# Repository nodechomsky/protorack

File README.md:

# protorack
A modular system for prototyping tools

The goal of this project is to produce a convergent set of standardized designs for intermodular featuring, fixturing, and dimensioning standard tools used in the process of developing hardware prototypes, specifically in the realm of electronic engineering and it's unique needs.

Standards/Objectives/Goals:

 -Intermodularity within the system to allow creative repurposing and open thought-space for the engineer

 -Interoperability with existing tools with an emphasis on common dimensioning standards found in other tools

 -Open Source and collaborative development of shared standards to allow ideas to be more easily synthesized and shared between collaborators

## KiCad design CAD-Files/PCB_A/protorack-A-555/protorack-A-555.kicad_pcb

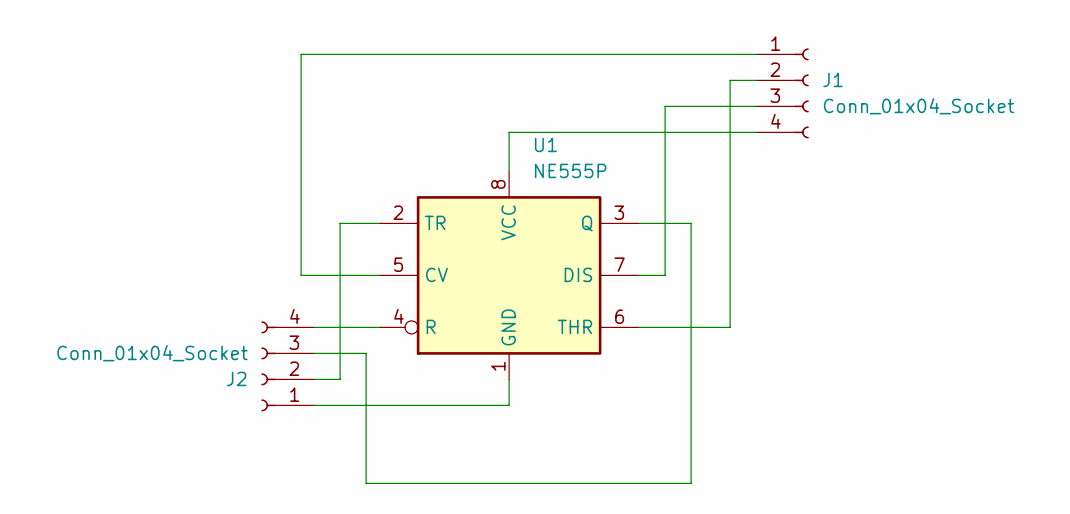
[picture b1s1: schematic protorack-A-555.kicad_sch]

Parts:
J1, J2: Conn_01x04_Socket; PinHeader_1x04_P2.54mm_Vertical
U1: NE555P; DIP-8_W7.62mm

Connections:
unnamed: J1.1, U1.5 (CV)
unnamed: J1.2, U1.6 (THR)
unnamed: J1.3, U1.7 (DIS)
unnamed: J1.4, U1.8 (VCC)
unnamed: J2.1, U1.1 (GND)
unnamed: J2.2, U1.2 (TR)
unnamed: J2.3, U1.3 (Q)
unnamed: J2.4, U1.4 (R)

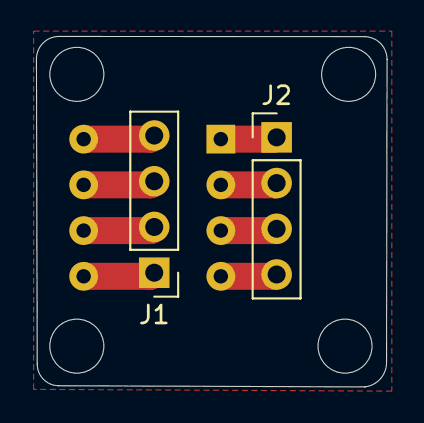
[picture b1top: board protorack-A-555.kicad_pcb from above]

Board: 2 copper layers, 19.5 x 19.5 mm, 3 parts (1 on the bottom side), 8 nets.

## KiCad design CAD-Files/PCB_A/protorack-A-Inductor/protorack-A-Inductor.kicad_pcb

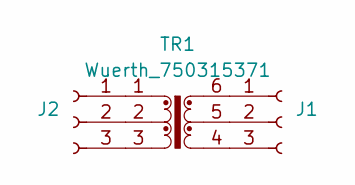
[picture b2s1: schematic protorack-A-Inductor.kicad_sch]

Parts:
J1, J2: Conn_01x03_Socket; PinHeader_1x03_P2.54mm_Vertical
TR1: Wuerth_750315371; Transformer_Wuerth_750315371

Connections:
unnamed: J1.1, TR1.6
unnamed: J1.2, TR1.5
unnamed: J1.3, TR1.4
unnamed: J2.1, TR1.1
unnamed: J2.2, TR1.2
unnamed: J2.3, TR1.3

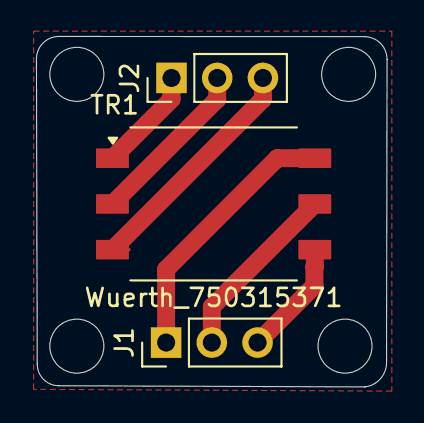
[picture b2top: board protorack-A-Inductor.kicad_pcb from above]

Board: 2 copper layers, 19.5 x 19.5 mm, 3 parts (0 on the bottom side), 6 nets.

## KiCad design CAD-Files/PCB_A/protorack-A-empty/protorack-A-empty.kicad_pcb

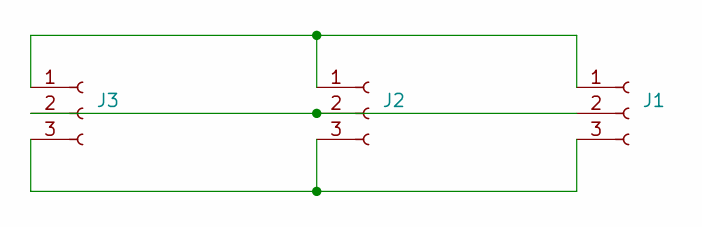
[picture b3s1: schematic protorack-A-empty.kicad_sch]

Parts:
J1, J2, J3: Conn_01x03_Socket; PinHeader_1x03_P2.54mm_Vertical

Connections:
unnamed: J1.1, J2.1, J3.1
unnamed: J1.2, J2.2, J3.2
unnamed: J1.3, J2.3, J3.3

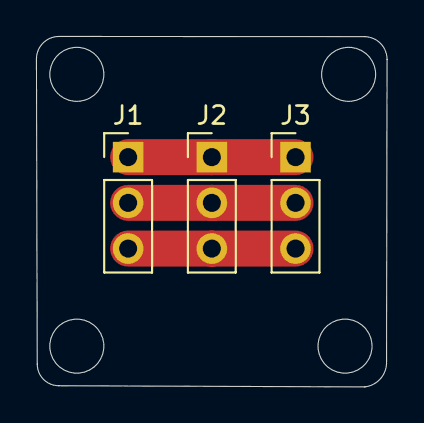
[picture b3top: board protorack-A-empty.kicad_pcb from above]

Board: 2 copper layers, 19.5 x 19.5 mm, 3 parts (0 on the bottom side), 3 nets.

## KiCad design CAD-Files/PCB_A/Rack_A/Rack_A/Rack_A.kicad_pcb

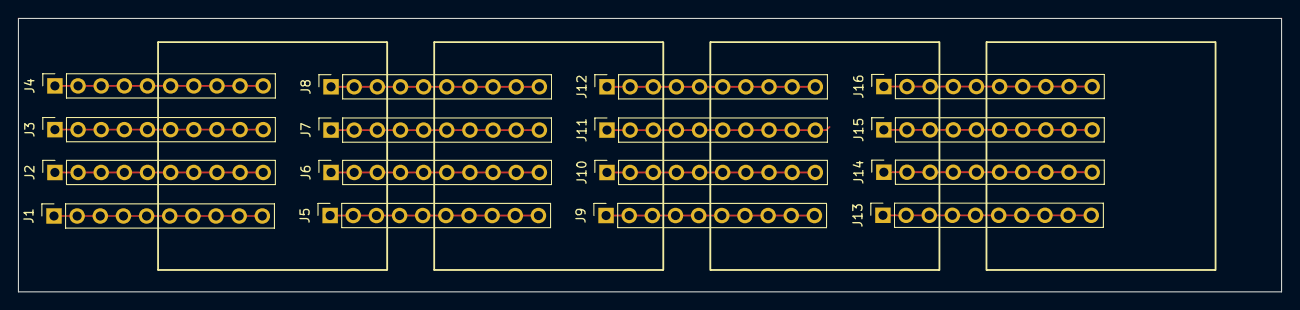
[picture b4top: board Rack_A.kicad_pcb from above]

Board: 2 copper layers, 138.6 x 30.0 mm, 16 parts (0 on the bottom side), 16 nets.

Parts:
J1, J2, J3, J4, J5, J6, J7, J8, J9, J10, J11, J12, J13, J14, J15, J16: Conn_01x10; PinSocket_1x10_P2.54mm_Vertical

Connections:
unnamed: J1.1, J1.2, J1.3, J1.4, J1.5, J1.6, J1.7, J1.8, J1.9, J1.10
unnamed: J2.1, J2.2, J2.3, J2.4, J2.5, J2.6, J2.7, J2.8, J2.9, J2.10
unnamed: J3.1, J3.2, J3.3, J3.4, J3.5, J3.6, J3.7, J3.8, J3.9, J3.10
unnamed: J4.1, J4.2, J4.3, J4.4, J4.5, J4.6, J4.7, J4.8, J4.9, J4.10
unnamed: J5.1, J5.2, J5.3, J5.4, J5.5, J5.6, J5.7, J5.8, J5.9, J5.10
unnamed: J6.1, J6.2, J6.3, J6.4, J6.5, J6.6, J6.7, J6.8, J6.9, J6.10
unnamed: J7.1, J7.2, J7.3, J7.4, J7.5, J7.6, J7.7, J7.8, J7.9, J7.10
unnamed: J8.1, J8.2, J8.3, J8.4, J8.5, J8.6, J8.7, J8.8, J8.9, J8.10
unnamed: J9.1, J9.2, J9.3, J9.4, J9.5, J9.6, J9.7, J9.8, J9.9, J9.10
unnamed: J10.1, J10.2, J10.3, J10.4, J10.5, J10.6, J10.7, J10.8, J10.9, J10.10
unnamed: J11.1, J11.2, J11.3, J11.4, J11.5, J11.6, J11.7, J11.8, J11.9, J11.10
unnamed: J12.1, J12.2, J12.3, J12.4, J12.5, J12.6, J12.7, J12.8, J12.9, J12.10
unnamed: J13.1, J13.2, J13.3, J13.4, J13.5, J13.6, J13.7, J13.8, J13.9, J13.10
unnamed: J14.1, J14.2, J14.3, J14.4, J14.5, J14.6, J14.7, J14.8, J14.9, J14.10
unnamed: J15.1, J15.2, J15.3, J15.4, J15.5, J15.6, J15.7, J15.8, J15.9, J15.10
unnamed: J16.1, J16.2, J16.3, J16.4, J16.5, J16.6, J16.7, J16.8, J16.9, J16.10

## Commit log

2025-01-31 first
2025-01-31 Outline added
2025-01-31 cleanup
2025-02-01 First CAD files
2025-02-01 First CAD files -cleanup
2025-02-01 Receptacle-first draft
2025-02-01 git sucks
2025-02-01 added PCB files
2025-02-04 additional PCBs
2025-02-04 Collada model included
2025-02-05 First Draft of Rack
2025-02-06 3x4 grid Rack daisy chain (delta) arrangement
2025-02-06 stl models and design files
